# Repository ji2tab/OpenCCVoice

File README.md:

# OpenCCVoice Project

[日本語 (Japanese)](#openccvoice-について) | [English](#about-openccvoice)

---

## OpenCCVoice について
OpenCCVoice は、**JA2CCV** 局の設計考案を基礎に、複数局の協力により発展してきたプロジェクトです。
このプロジェクトは、技術を共有し、改善し合い、より良いものへ発展させていくことを目的としています。

### 理念：ブラックボックスにしない、共有の精神
OpenCCVoice はアマチュア無線の精神に基づき、以下の理念を掲げています。

> **「誰でも自由に使え、誰でも改良でき、そしてその成果をオープンに共有できる」**

特定の人だけが技術を抱え込む「ブラックボックス化」を避け、多くの局が改善に参加することで、技術の相互発展を促します。
この理念を象徴するものとして**「OpenCCVoice」**という名称が付けられています。

### ライセンスと権利について
公開予定の回路図、Arduino スケッチ、基板データ、関連ドキュメントの著作権は **JA2CCV 局および OpenCCVoice プロジェクト** に帰属します。

OpenCCVoice は、技術共有と発展を目的としたオープンプロジェクトであり、公開物は **オープンソースライセンス（GPL v3 の理念に準拠）** のもとで取り扱われます。

#### 1. 利用と改変について
* どなたでも **自由に利用** できます。
* 必要に応じて **改変・機能追加・組み込み** が可能です。

#### 2. 再配布・派生物公開の条件（コピーレフト）
改変版や派生物を公開・配布する際は、以下の条件を遵守してください。

1.  **原著作者（JA2CCV／OpenCCVoice）を明示すること**
2.  **改変した点を明記すること**
3.  **派生物も同じくオープンな形で公開すること**
    * ブラックボックス化せず、ソースコード・回路図・基板データ等を公開してください。

#### 3. ライセンス文書について
正式な LICENSE（GPL v3）文書は、回路図・ソフトウェア・基板データ公開時に同梱されます。

OpenCCVoice が多くの局とともに発展していくことを願っています。

### 免責事項 (Disclaimer)
本プロジェクトで公開されているハードウェア設計（回路図・基板データ）、ソフトウェア（ソースコード）、および関連ドキュメントの利用にあたっては、以下の事項をあらかじめご了承ください。

1.  **無保証（No Warranty）**
    本成果物は「現状のまま（As Is）」で提供されます。製作者およびOpenCCVoiceプロジェクトは、特定の目的への適合性、動作の確実性、およびバグや不具合がないことを保証しません。
2.  **損害に対する非責任**
    本成果物の使用、または使用不能によって生じた、いかなる損害（無線機・PC等のハードウェア故障、データの消失、火災、怪我など）についても、製作者およびプロジェクトメンバーは一切の責任を負いません。自作機器の接続は、ご自身の無線機を破損させるリスクがあることを理解した上で行ってください。
3.  **法令の遵守（Legal Compliance）**
    本装置を使用して無線局を運用する場合、利用者は各国の電波法および関連法規（日本国内においては電波法、無線局運用規則など）を遵守する責任を負います。
    * 送信間隔、送出内容、変調レベルなどが法的基準を満たしているか、利用者の責任において確認・調整してください。
    * 本装置の使用による法令違反について、製作者は一切関知しません。
4.  **ライセンス**
    本プロジェクトは **GPL v3 (GNU General Public License v3)** の下で公開されています。再配布や改変に関する条件はライセンス条項に従ってください。

---

## About OpenCCVoice
The OpenCCVoice project is based on the design and concept by **JA2CCV**, and has been developed through the cooperation of multiple stations.
The goal of this project is to share technology, improve upon it together, and foster further development.

### Philosophy: No Black Box, Spirit of Sharing
Based on the spirit of Amateur Radio, OpenCCVoice upholds the following philosophy:

> **"Free to use, free to improve, and results are shared openly."**

We aim to avoid "black boxing"—where technology is hoarded by a few—and instead encourage mutual technological advancement by allowing many stations to participate in improvements.
The name **"OpenCCVoice"** was chosen to symbolize this philosophy.

### License and Rights
The copyright of the schematics, Arduino sketches, PCB data, and related documentation belongs to **JA2CCV and the OpenCCVoice Project**.

OpenCCVoice is an open project aimed at technology sharing and development. All published materials are handled under **Open Source Licenses (compliant with GPL v3 principles)**.

#### 1. Usage and Modification
* Anyone is **free to use** this project.
* You may **modify, add features, or integrate** it as needed.

#### 2. Conditions for Redistribution (Copyleft)
When publishing or distributing modified versions or derivatives, you must observe the following conditions:

1.  **Credit the original authors (JA2CCV / OpenCCVoice).**
2.  **Clearly state the modifications made.**
3.  **Release the derivative works under the same open terms.**
    * Do not "black box" the project; you must publish the source code, schematics, and PCB data.

#### 3. About License Documents
The official LICENSE (GPL v3) document will be included with the release of schematics, software, and PCB data.

We hope that OpenCCVoice will continue to grow together with many stations.

### Disclaimer
Please read the following terms carefully before using the hardware designs (schematics, PCB data), software (source code), and documentation provided by the OpenCCVoice project.

1.  **No Warranty**
    This project is provided "AS IS", without warranty of any kind, express or implied, including but not limited to the warranties of merchantability or fitness for a particular purpose. The entire risk as to the quality and performance of the project is with you.
2.  **Limitation of Liability**
    In no event shall the authors or copyright holders be liable for any claim, damages, or other liability, whether in an action of contract, tort, or otherwise, arising from, out of, or in connection with the software/hardware or the use or other dealings in the project.
    * **Hardware Risk:** Connecting custom circuits to your radio equipment carries inherent risks. You assume full responsibility for any damage to your transceiver, computer, or other devices.
3.  **Regulatory Compliance**
    Users are solely responsible for complying with the radio laws and regulations of their respective countries or regions.
    * It is the user's responsibility to ensure that transmission intervals, audio levels, and operation methods comply with local legal requirements.
    * The authors assume no responsibility for any legal violations committed by the user.
4.  **License**
    This project is released under the **GNU General Public License v3 (GPL v3)**. Please refer to the license for terms regarding redistribution and modification.

---
**Project Contributors:** JA2CCV, JA9HYM, JA2DML, JG1XWV, JI2TAB

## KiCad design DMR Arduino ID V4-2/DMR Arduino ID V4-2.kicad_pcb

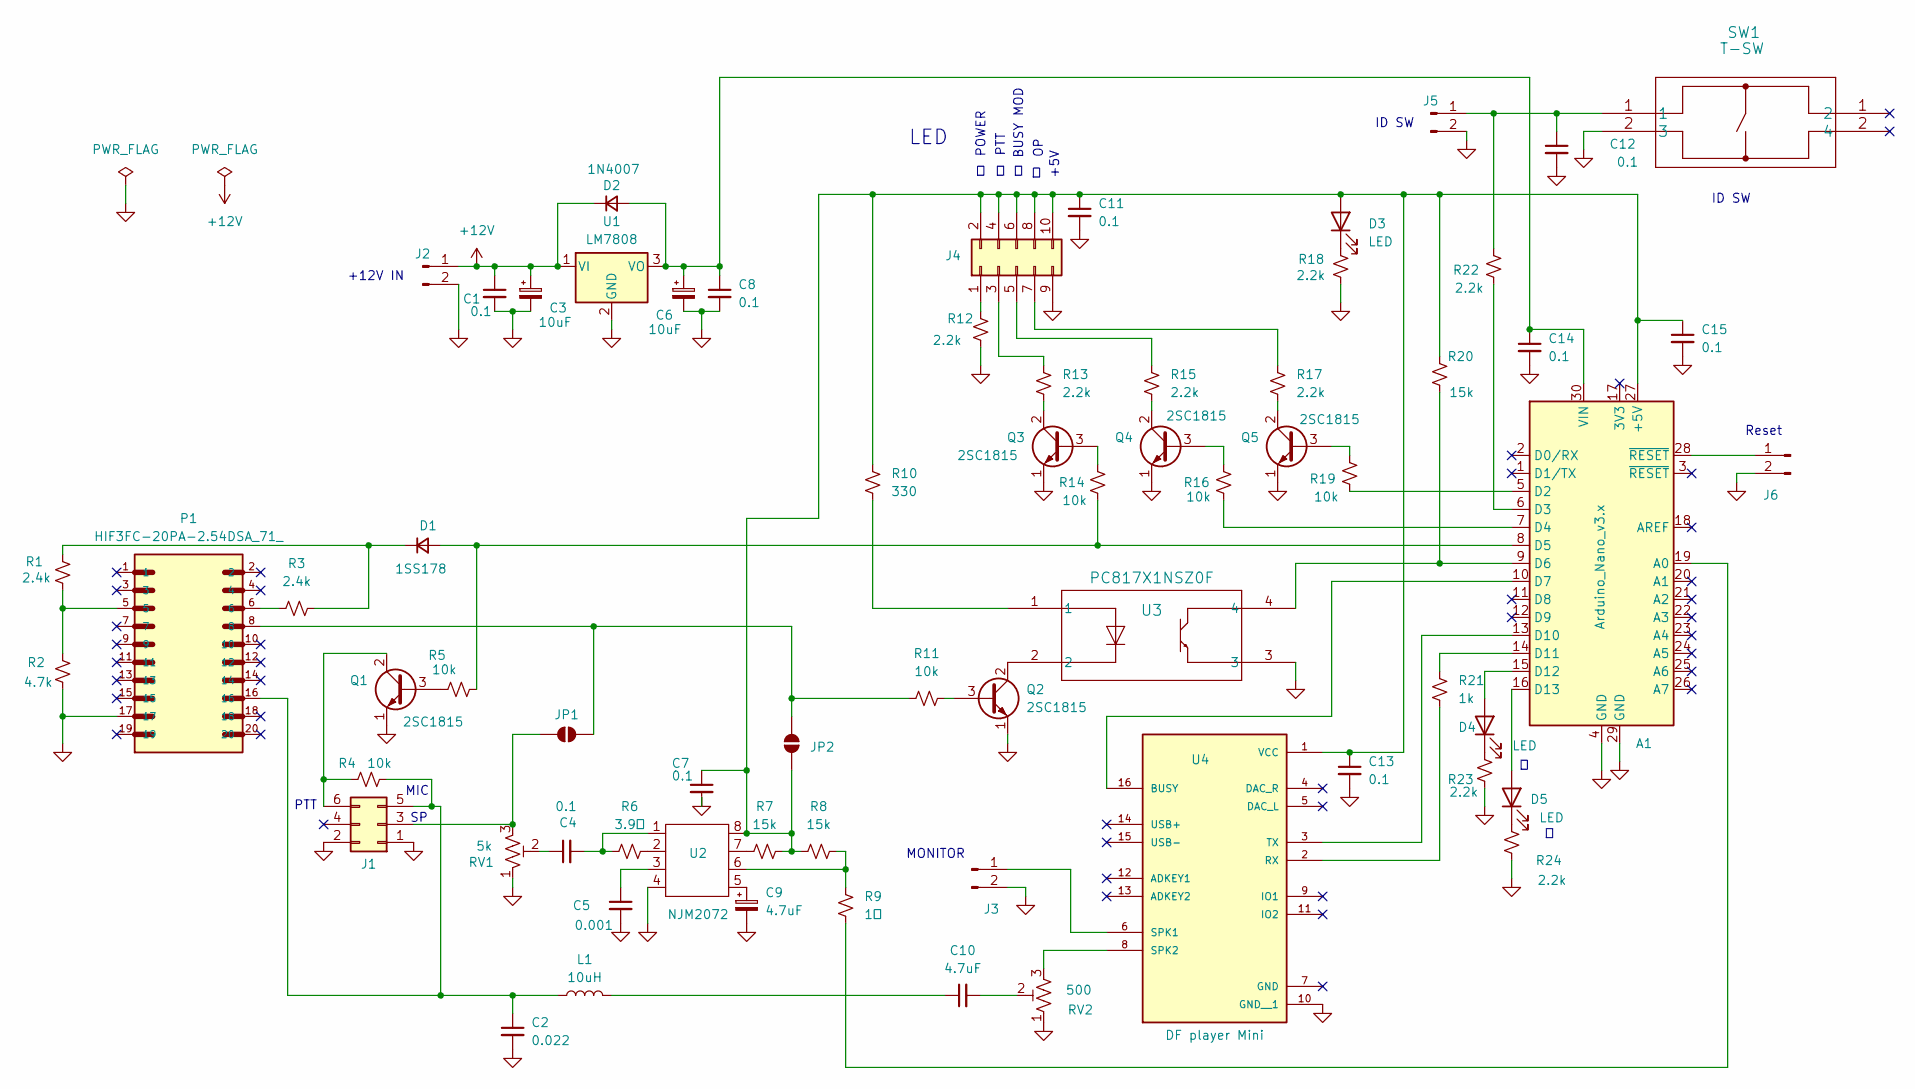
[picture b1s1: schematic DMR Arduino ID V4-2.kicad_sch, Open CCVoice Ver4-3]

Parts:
A1: Arduino_Nano_v3.x; Arduino_Nano_WithMountingHoles
C1, C4, C7, C8, C11, C12, C13, C14, C15: 0.1; C_Disc_D4.3mm_W1.9mm_P5.00mm
C2: 0.022; C_Disc_D4.3mm_W1.9mm_P5.00mm
C3, C6: 10uF; CP_Radial_D5.0mm_P2.50mm
C5: 0.001; C_Disc_D4.3mm_W1.9mm_P5.00mm
C9: 4.7uF; CP_Radial_D5.0mm_P2.50mm
C10: 4.7uF; C_Radial_D5.0mm_H5.0mm_P2.00mm
D1: 1SS178; D_DO-34_SOD68_P7.62mm_Horizontal
D2: 1N4007; D_DO-34_SOD68_P10.16mm_Horizontal
D3, D4, D5: LED; LED_D3.0mm_FlatTop
J1: Conn_02x03_Odd_Even; PinHeader_2x03_P2.54mm_Vertical
J2, J3, J5, J6: Conn_01x02_Pin; PinHeader_1x02_P2.54mm_Vertical
J4: Conn_02x05_Odd_Even; PinHeader_2x05_P2.54mm_Vertical
JP1, JP2: SolderJumper_2_Open; SolderJumper-2_P1.3mm_Open_RoundedPad1.0x1.5mm
L1: 10uH; L_Axial_L5.3mm_D2.2mm_P7.62mm_Horizontal_Vishay_IM-1
P1: HIF3FC-20PA-2.54DSA_71_; IDC-Header_2x10_P2.54mm_Horizontal
Q1, Q2, Q3, Q4, Q5: 2SC1815; TO-92L_Inline_Wide
R1, R3: 2.4k; R_Axial_DIN0204_L3.6mm_D1.6mm_P7.62mm_Horizontal
R2: 4.7k; R_Axial_DIN0204_L3.6mm_D1.6mm_P7.62mm_Horizontal
R4, R5, R11, R14, R16, R19: 10k; R_Axial_DIN0204_L3.6mm_D1.6mm_P7.62mm_Horizontal
R6: 3.9ｋ; R_Axial_DIN0204_L3.6mm_D1.6mm_P7.62mm_Horizontal
R7, R8, R20: 15k; R_Axial_DIN0204_L3.6mm_D1.6mm_P7.62mm_Horizontal
R9: 1ｋ; R_Axial_DIN0204_L3.6mm_D1.6mm_P7.62mm_Horizontal
R10: 330; R_Axial_DIN0204_L3.6mm_D1.6mm_P7.62mm_Horizontal
R12, R13, R15, R17, R18, R22, R23, R24: 2.2k; R_Axial_DIN0204_L3.6mm_D1.6mm_P7.62mm_Horizontal
R21: 1k; R_Axial_DIN0204_L3.6mm_D1.6mm_P7.62mm_Horizontal
RV1: 5k; Potentiometer_Bourns_3339P_Vertical
RV2: 500; Potentiometer_Bourns_3339P_Vertical
SW1: T-SW; B3F-1060
U1: LM7808; TO-220-3_Vertical
U2: NJM2072; CERDIP-8_W7.62mm_SideBrazed_Socket
U3: PC817X1NSZ0F; DIP-4_W7.62mm
U4: DFR0299; MODULE_DFR0299

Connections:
+12V: C1.1, C3.1, D2.1 (K), J2.1, U1.1 (VI)
GND: A1.4 (GND), A1.29 (GND), C1.2, C2.2, C3.2, C5.2, C6.2, C7.2, C8.2, C9.2, C11.2, C12.2, C13.2, C14.2, C15.2, J1.1, J1.2, J2.2, J3.2, J4.9, J5.2, J6.2, P1.17, Q1.1 (E), Q2.1 (E), Q3.1 (E), Q4.1 (E), Q5.1 (E), R2.2, R12.2, R18.2, R23.2, R24.2, RV1.1, RV2.1, SW1.2 (3), U1.2 (GND), U2.4, U3.3, U4.10 (GND__1)
unnamed: A1.27 (+5V), C7.1, C11.1, C13.1, C15.1, D3.2 (A), J4.2, J4.4, J4.6, J4.8, J4.10, JP2.1 (A), R7.2, R8.1, R10.1, R20.1, U2.8, U4.1 (VCC)
unnamed: A1.19 (A0), R9.2
unnamed: A1.5 (D2), R19.2
unnamed: A1.6 (D3), R22.2
unnamed: A1.7 (D4), R16.2
unnamed: A1.8 (D5), D1.2 (A), R5.2, R14.2
unnamed: A1.9 (D6), R20.2, U3.4
unnamed: A1.10 (D7), U4.16 (BUSY)
unnamed: A1.13 (D10), U4.3 (TX)
unnamed: A1.14 (D11), R21.1
unnamed: A1.15 (D12), D4.2 (A)
unnamed: A1.16 (D13), D5.2 (A)
unnamed: A1.30 (VIN), C6.1, C8.1, C14.1, D2.2 (A), U1.3 (VO)
unnamed: C4.1, RV1.2
unnamed: C4.2, R6.1, U2.1
unnamed: C5.1, U2.3
unnamed: C9.1, U2.5
unnamed: C10.1, L1.2
unnamed: C10.2, RV2.2
unnamed: D1.1 (K), R1.1, R3.1
unnamed: D3.1 (K), R18.1
unnamed: D4.1 (K), R23.1
unnamed: D5.1 (K), R24.1
unnamed: J1.3, JP1.1 (A), RV1.3
unnamed: C2.1, J1.5, L1.1, P1.16, R4.2
unnamed: J1.6, Q1.2 (C), R4.1
unnamed: J3.1, U4.6 (SPK1)
unnamed: J4.1, R12.1
unnamed: J4.3, R13.1
unnamed: J4.5, R15.1
unnamed: J4.7, R17.1
unnamed: C12.1, J5.1, R22.1, SW1.1
unnamed: A1.28 (~RESET), J6.1
unnamed: JP1.2 (B), JP2.2 (B), P1.8, R11.1
unnamed: P1.5, R1.2, R2.1
unnamed: P1.6, R3.2
unnamed: Q1.3 (B), R5.1
unnamed: Q2.3 (B), R11.2
unnamed: Q2.2 (C), U3.2
unnamed: Q3.3 (B), R14.1
unnamed: Q3.2 (C), R13.2
unnamed: Q4.3 (B), R16.1
unnamed: Q4.2 (C), R15.2
unnamed: Q5.3 (B), R19.1
unnamed: Q5.2 (C), R17.2
unnamed: R6.2, U2.2
unnamed: R7.1, U2.7
unnamed: R8.2, R9.1, U2.6
unnamed: R10.2, U3.1
unnamed: R21.2, U4.2 (RX)
unnamed: RV2.3, U4.8 (SPK2)

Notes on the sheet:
+12V IN
Reset
LED
+5V
BUSY MOD
MIC
MONITOR
ID SW
PTT
POWER

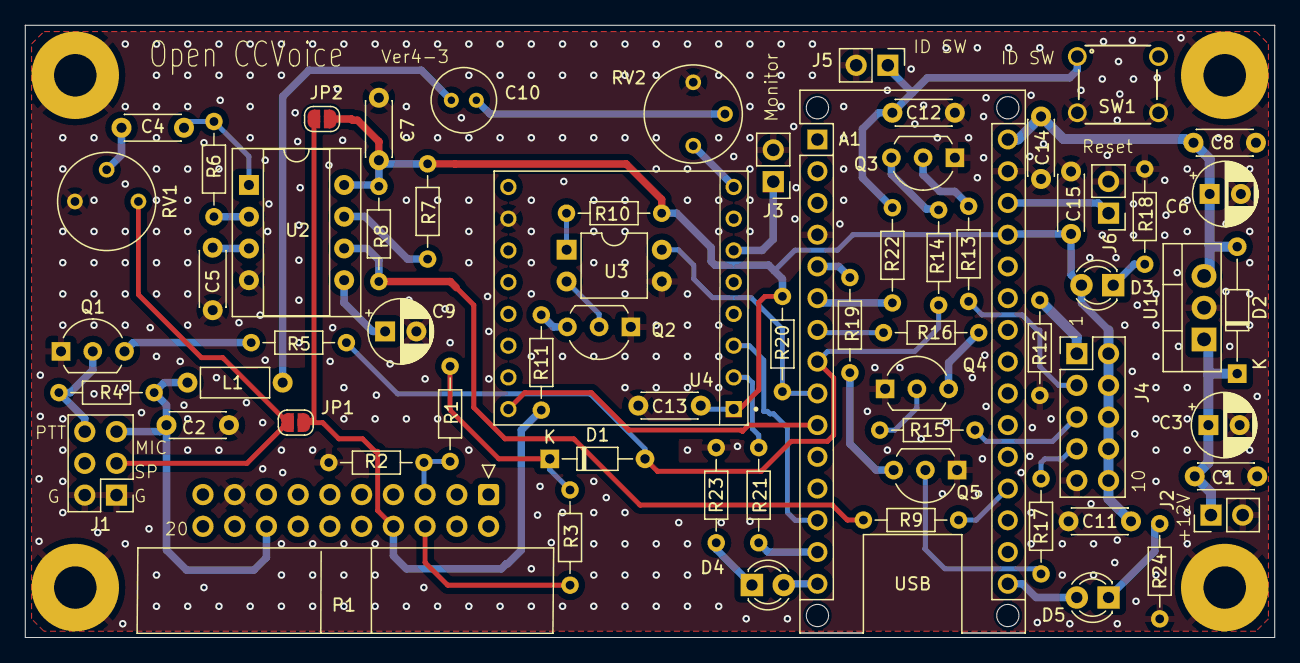
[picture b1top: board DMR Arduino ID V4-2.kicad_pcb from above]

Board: 2 copper layers, 100.0 x 49.0 mm, 67 parts (0 on the bottom side), 53 nets.

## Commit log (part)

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2026-01-21 Expand README with usage instructions and troubleshooting
    Added detailed user manual and command reference for OpenCCVoice.
2026-01-21 Create 'about us' file for OpenCCVoice project
    Added project details, licensing information, and usage guidelines for OpenCCVoice.
2026-01-21 Add CCVoice 1.72 final EEPROM F firmware
2026-01-21 Create CHANGELOG.md for CCVoice project
    Added a comprehensive changelog for the TM-8250 ID Guidance Controller project, detailing version history, features, fixes, and enhancements.
2026-01-21 Update project name in comments
2026-01-21 Add test file
2026-01-21 Create test
2026-01-21 Add directory structure for OpenCCVoice project
2026-01-21 Update directory
2026-01-22 Rename CCVoice_1_72_final_EEPROM_F.ino to firmware/old_versions/CCVoice_1_72_final_EEPROM_F.ino
2026-01-22 Rename CHANGELOG.md to firmware/old_versions/CHANGELOG/v1.72-final-EEPROM+F.CHANGELOG.md
2026-01-22 Rename firmware/old_versions/CCVoice_1_72_final_EEPROM_F.ino to firmware/old_versions/CCVoice_1_72_final_EEPROM_F/CCVoice_1_72_final_EEPROM_F.ino
2026-01-22 Rename firmware/old_versions/CHANGELOG/v1.72-final-EEPROM+F.CHANGELOG.md to firmware/old_versions/CHANGELOG.md
2026-01-22 Rename firmware/old_versions/CHANGELOG.md to firmware/old_versions/CCVoice_1_72_final_EEPROM_F/CHANGELOG.md
2026-01-22 Rename README.md to firmware/old_versions/CCVoice_1_72_final_EEPROM_F/README.md
2026-01-23 Initialize README.md with project information
    Add detailed project overview, licensing, and disclaimers.
2026-01-23 Revise README structure and content
    Updated README.md to enhance structure and clarity, including sections on philosophy, license, and disclaimer.
2026-01-31 Create PartsList
2026-02-19 Create memo
2026-03-02 Create Arduino-IDE.html
    Arduino IDE導入方法
    2025/03/03 堀江作成
2026-05-13 Create DVSwitch × Pi-Star 自動音声応答システム構築手順書 (V1.44準拠)
2026-05-13 Update DVSwitch × Pi-Star 自動音声応答システム構築手順書 (V1.44準拠)
2026-05-13 Rename DVSwitch × Pi-Star 自動音声応答システム構築手順書 (V1.44準拠) to DVSwitch × Pi-Star 自動音声応答システム構築手順書 (V1.44準拠).md

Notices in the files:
parts and their libraries:
Copyright 2016 Accelerated Designs. All rights reserved.
